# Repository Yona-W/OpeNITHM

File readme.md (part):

# OpeNITHM

This repository contails files related to OpeNITHM.

Firmware, schematics, board layout, and CAD files are included in this repo. Please see the CAD directory for the original 3d printed version, or the v2-cad directory for the laser cut version. 

## List of Hardware

In the `CAD\STL` folder, you will find numerous parts that must be 3D printed.

Please check out [the wiki](https://github.com/veroxzik/OpeNITHM/wiki/File-Explanation) for more information.

| Part | Qty |
| --- |:---:|
| Center Frame | 1 |
| Right Frame | 1 |
| Left Frame | 1 |
| Key Dual 2.5mm **OR** Key Dual 3mm<sup>1</sup> | 16 |
| LED Support Peg | 16 |
| Sensor Rail | 2 |
| Sensor Spacer Left<sup>2</sup> | 1 |
| Sensor Base Left<sup>2</sup> **OR** Integrated Sensor Base Left<sup>2</sup> | 1 |
| Sensor Cover Left<sup>2</sup> | 1 |
| Integrated Frame Mount Left<sup>2,3</sup> | 1 |

**NOTES:** 
1. Use 2.5mm for 3/32" and 3mm for 1/8" acrylic. 
2. Print out mirrored version of these parts as well.
3. Only print the frame mount if you are using the integrated sensor.

The non-printed materials and hardware include:

| Part                                                                       | Qty |
| --- |:---:|
| 4-40 Flat Head Screw, length 3/16" to 5/16" will work **OR** M3 equivalent | 2   |
| Top Acrylic Plate<sup>1</sup> (472mm x 112mm)                              | 1   |
| Key Acrylic<sup>1</sup> (103.5mm x 26mm)                                   | 16  |
| Copper Tape, cut into rectangles 95mm x 26mm                               | 16  |

**NOTES:**
1. Use 2.5mm (3/32") **OR** 3mm (1/8") acrylic. Use the same acrylic for top plate and keys.

## List of Electronics

OpeNITHM is designed for the Teensy LC.

#### Why use Teensy and not Arduino?

The biggest reason is that Teensy has built in capacitive sensing, which is how OpeNITHM fuctions. You have to fake it on Arduino using very controlled analog reads, and it is nowhere near as sensitive. In my (VXZK's) experience, it was simply impossible to use an Arduino to do the capacitive sensing required for this project.

I chose the Teensy LC as it is the lowest cost Teensy model available with capacitive sensing. The firmware and PCB are designed for this board alone; significant modifications may be required for any other version.

There is an alternative build using an Arduino Pro Micro and 2 MPR121s as a branch in this repo, but it is not maintained and not recommended. You're on your own with that one!

### Teensy LC Build

Links are mostly suggestions (except the Teensy, which is only officially available through the PJRC site and authorized resellers).  
(VXZK: I've heard a lot of trouble regarding good quality IR leds and phototransistors, so I've included specific links to the ones I purchased and has worked well for me.)  

The links below also assume you want to socket your Teensy and multiplexers for later use. You can solder them directly, if you'd like.  
If you are going to solder your sensors directly to the PCB, it is not necessary buy the 0.1" Pin Header, Right Angle. Otherwise, include female 0.1" sockets for your sensors (commonly referred to as Dupont connectors).  

| Part | Link | Qty |
| --- | --- |:---:|
| Teensy LC | https://www.pjrc.com/store/teensylc.html | 1 |
| Teensy LC Breakout Board | this Github, Circuit-Teensy32 folder contains gerbers | 1 |
| 74HC4051 Multiplexer Breakout Board | [Aliexpress][1] | 4 |
| 0.1" Pin Header, 1 row, 40 pos | [Aliexpress (qty 10)][2] | 2 |
| 0.1" Pin Header, Right Angle, 2 row, 24 pos | [LCSC][3] | 2 |
| 0.1" Socket, Straight, 1 row, 14 pos | [LCSC][4] | 2 |
| 0.1" Socket, Straight, 1 row, 5 pos | [LCSC][5] | 2 |
| 0.1" Socket, Straight, 1 row, 11 pos | [LCSC][6] | 2 |
| 0.1" Socket, Straight, 1 row, 8 pos | [LCSC][7] | 2 |
| 51k ohm Resistor, 1/6W or 1/8W | LCSC or Aliexpress | 6 |
| 33 ohm Resistor, 1/4W, 1/6W, or 1/8W | LCSC or Aliexpress | 3 |
| 1m WS2812B RGB 5V LED Strip, 30LED Per Meter | [Aliexpress][8] | 1 |
| IR LED and Phototransistor | [Ebay (Qty 20 pairs)][9] | 6 |

[1]: https://www.aliexpress.com/item/32807771098.html
[2]: https://www.aliexpress.com/item/665534073.html
[3]: https://lcsc.com/product-detail/New-Arrivals_XFCN-PZ254R-12-24P_C492440.html
[4]: https://lcsc.com/product-detail/Pin-Header-Female-Header_Boom-Precision-Elec-Female-header-2-54-1-14P_C52711.html
[5]: https://lcsc.com/product-detail/Pin-Header-Female-Header_Boom-Precision-Elec-2-54mm-1-5p-Female-header_C50950.html
[6]: https://lcsc.com/product-detail/Pin-Header-Female-Header_Changjiang-Connectors-A2541HWV-11P_C225508.html
[7]: https://lcsc.com/product-detail/Pin-Header-Female-Header_Boom-Precision-Elec-2-54mm-1-8P-Straight-Female-header_C27438.html
[8]: https://www.aliexpress.com/item/2036819167.html
[9]: https://www.ebay.com/itm/40pcs-5mm-Infrared-LED-940nm-Emitter-Diode-and-IR-Receiver-Set/252235145540

## Board Revision and Sensors

As of 2020-07-17, the recommended board version is v2.1, which features inputs for 32 sensors. This best replicates the feeling of the arcade. Previous versions used 16 sensors. If you still wish to make a 16 key version, you can order the v2.1 but only populate two of the multiplexers. This is not really recommended.

## Installing on Teensy LC

**NOTE:** This firmware is *only* written to work for the Teensy LC. Do *not* use Teensy 2.0 or Teensy 3.x

Skip this section if you are using a Pro Micro.

Locate your `arduino` folder (usually `C:\Program Files (x86)\arduino`).

#### I have a fresh install of Teensyduino, or have never modified my USB profiles

Copy `Firmware/Teensy/boards.txt` to `arduino\hardware\teensy\avr\` and overwrite the existing.

Copy `Firmware/Teensy/teensy3` to `arduino\hardware\teensy\avr\cores\teensy3` and overwrite any conflicts.

Copy `Firmware/FastLED/WS2812Serial.cpp` and `Firmware/FastLED/WS2812Serial.h` to `arduino\hardware\teensy\avr\libraries\WS2812Serial` and overwrite the existing.

Copy `Firmware/FastLED/FastLED.cpp` and `Firmware/FastLED/FastLED.h` to `[My Documents]\Arduino\libraries\FastLED\` and overwrite the existing.

#### I am applying the changes manually

(It is easier to copy and paste from the files in `Firmware/Teensy` instead of through here, the below is just for reference.)

Add `usb_nkro.c` and `usb_nkro.h` to `arduino\hardware\teensy\avr\cores\teensy3`

In `arduino\hardware\teesny\avr\boards.txt` add lines 1175-1179

```c
1175    teensyLC.menu.usb.nkrokeyboard=NKRO Keyboard
1176    teensyLC.menu.usb.nkrokeyboard.build.usbtype=USB_NKRO
1177    teensyLC.menu.usb.nkrokeyboard.fake_serial=teensy_gateway
1178    teensyLC.menu.usb.serialnkrokeyboard=Serial + NKRO Keyboard
1179    teensyLC.menu.usb.serialnkrokeyboard.build.usbtype=USB_SERIAL_NKRO

In `arduino\hardware\teensy\avr\cores\teensy3\WProgram.h` add line 59

```c
58    #include "usb_joystick.h"
59    #include "usb_nkro.h"
60    #include "usb_midi.h"
```

In `arduino\hardware\teensy\avr\cores\teensy3\usb_inst.cpp` add lines 75-77

```c
72    usb_serial_class Serial;
73    #endif
74    
75    #ifdef NKRO_INTERFACE
76    usb_nkro_class Nkro;
77    #endif
78    
79    #else // F_CPU < 20 MHz
```

In `arduino\hardware\teensy\avr\cores\teensy3\usb_dev.h` add lines 93-98

```c
90    extern volatile uint8_t keyboard_leds;
91    #endif
92    
93    #ifdef NKRO_INTERFACE
94    extern uint8_t nkro_report_data[NKRO_SIZE];
95    extern uint8_t nkro_protocol;
96    extern uint8_t nkro_idle_config;
97    extern uint8_t nkro_idle_count;
98    #endif
99    
100   #ifdef MIDI_INTERFACE
```

In `arduino\hardware\teensy\avr\cores\teensy3\usb_desc.h` add lines 868-948

```c
866      #define ENDPOINT15_CONFIG	ENDPOINT_TRANSMIT_ONLY
867    
868    #elif defined(USB_NKRO)
869      #define VENDOR_ID		0x16C0
870      #define PRODUCT_ID		0x04D0
871      #define MANUFACTURER_NAME	{'T','e','e','n','s','y','d','u','i','n','o'}
872      #define MANUFACTURER_NAME_LEN	11
873      #define PRODUCT_NAME		{'N','K','R','O',' ','K','e','y','b','o','a','r','d'}
874     #define PRODUCT_NAME_LEN	13
875      #define EP0_SIZE		64
876      #define NUM_ENDPOINTS         5
877      #define NUM_USB_BUFFERS	14
878      #define NUM_INTERFACE		4
879      #define SEREMU_INTERFACE      1	// Serial emulation
880      #define SEREMU_TX_ENDPOINT    1
881      #define SEREMU_TX_SIZE        64
882      #define SEREMU_TX_INTERVAL    1
883      #define SEREMU_RX_ENDPOINT    2
884      #define SEREMU_RX_SIZE        32
885      #define SEREMU_RX_INTERVAL    2
886      #define KEYBOARD_INTERFACE    0	// Keyboard
887      #define KEYBOARD_ENDPOINT     3
888      #define KEYBOARD_SIZE         8
889      #define KEYBOARD_INTERVAL     1
890      #define KEYMEDIA_INTERFACE    2	// Keyboard Media Keys
891      #define KEYMEDIA_ENDPOINT     4
892      #define KEYMEDIA_SIZE         8
893      #define KEYMEDIA_INTERVAL     4
894      #define NKRO_INTERFACE        3	// NKRO Keyboard
895      #define NKRO_ENDPOINT         5
896      #define NKRO_SIZE             32
897      #define NKRO_REPORT_KEYS		( NKRO_SIZE - 1 )
898      #define NKRO_INTERVAL         1
899      #define ENDPOINT1_CONFIG	ENDPOINT_TRANSMIT_ONLY
900      #define ENDPOINT2_CONFIG	ENDPOINT_RECEIVE_ONLY
901      #define ENDPOINT3_CONFIG	ENDPOINT_TRANSMIT_ONLY
902      #define ENDPOINT4_CONFIG	ENDPOINT_TRANSMIT_ONLY
903      #define ENDPOINT5_CONFIG	ENDPOINT_TRANSMIT_ONLY
904      #define ENDPOINT6_CONFIG	ENDPOINT_TRANSMIT_ONLY
905
906    #elif defined(USB_SERIAL_NKRO)
907      #define VENDOR_ID		0x16C0
908      #define PRODUCT_ID		0x0487
909      #define DEVICE_CLASS		0xEF
910      #define DEVICE_SUBCLASS	0x02
911      #define DEVICE_PROTOCOL	0x01
912      #define MANUFACTURER_NAME	{'T','e','e','n','s','y','d','u','i','n','o'}
913      #define MANUFACTURER_NAME_LEN	11
914      #define PRODUCT_NAME		{'S','e','r','i','a','l','/','N','K','R','O',' ','K','e','y','b','o','a','r','d'}
915      #define PRODUCT_NAME_LEN	20
916      #define EP0_SIZE		64
917      #define NUM_ENDPOINTS         6
918      #define NUM_USB_BUFFERS	14
919      #define NUM_INTERFACE		5
920      #define CDC_IAD_DESCRIPTOR	1
921      #define CDC_STATUS_INTERFACE	0
922      #define CDC_DATA_INTERFACE	1	// Serial
923      #define CDC_ACM_ENDPOINT	2
924      #define CDC_RX_ENDPOINT       3
925      #define CDC_TX_ENDPOINT       4
926      #define CDC_ACM_SIZE          16
927      #define CDC_RX_SIZE           64
928      #define CDC_TX_SIZE           64
929      #define KEYBOARD_INTERFACE    2	// Keyboard
930      #define KEYBOARD_ENDPOINT     1
931      #define KEYBOARD_SIZE         8
932      #define KEYBOARD_INTERVAL     1
933      #define KEYMEDIA_INTERFACE    3	// Keyboard Media Keys
934      #define KEYMEDIA_ENDPOINT     5
935      #define KEYMEDIA_SIZE         8
936      #define KEYMEDIA_INTERVAL     4
937      #define NKRO_INTERFACE        4	// NKRO Keyboard
938      #define NKRO_ENDPOINT         6
939      #define NKRO_SIZE             32
940      #define NKRO_REPORT_KEYS		( NKRO_SIZE - 1 )
941      #define NKRO_INTERVAL         1
942      #define ENDPOINT1_CONFIG	ENDPOINT_TRANSMIT_ONLY
943      #define ENDPOINT2_CONFIG	ENDPOINT_TRANSMIT_ONLY
944      #define ENDPOINT3_CONFIG	ENDPOINT_RECEIVE_ONLY
945      #define ENDPOINT4_CONFIG	ENDPOINT_TRANSMIT_ONLY
946      #define ENDPOINT5_CONFIG	ENDPOINT_TRANSMIT_ONLY
947      #define ENDPOINT6_CONFIG	ENDPOINT_TRANSMIT_ONLY
948    #endif
949    
950    #ifdef USB_DESC_LIST_DEFINE
```

In `arduino\hardware\teensy\avr\cores\teensy3\usb_desc.c` add lines 239-265

```c
236    };
237    #endif
238    
239    #ifdef NKRO_INTERFACE
240    // Via https://dawnmist.dreamwidth.org/1250.html
241    static uint8_t nkro_hid_report_desc[] = {
242            0x05, 0x01, // Usage Page (Generic Desktop),
243            0x09, 0x06, // Usage (Keyboard),
244            0xA1, 0x01, // Collection (Application),
245            // bitmap of modifiers
246            0x75, 0x01, // Report Size (1),
247            0x95, 0x08, // Report Count (8),
248            0x05, 0x07, // Usage Page (Key Codes),
249            0x19, 0xE0, // Usage Minimum (224),
250            0x29, 0xE7, // Usage Maximum (231),
251            0x15, 0x00, // Logical Minimum (0),
252            0x25, 0x01, // Logical Maximum (1),
253            0x81, 0x02, // Input (Data, Variable, Absolute), ;Modifier byte
254            // bitmap of keys
255            0x95, NKRO_REPORT_KEYS*8, // Report Count (),
256            0x75, 0x01, // Report Size (1),
257            0x15, 0x00, // Logical Minimum (0),
258            0x25, 0x01, // Logical Maximum(1),
259            0x05, 0x07, // Usage Page (Key Codes),
260            0x19, 0x00, // Usage Minimum (0),
261            0x29, NKRO_REPORT_KEYS*8-1, // Usage Maximum (),
262            0x81, 0x02, // Input (Data, Variable, Absolute),
263            0xc0 // End Collection
264    };
265    #endif
266    
267    #ifdef JOYSTICK_INTERFACE
268    #if JOYSTICK_SIZE == 12
```

In `arduino\hardware\teensy\avr\cores\teensy3\usb_desc.c` add lines 603-610 and modify line 612

```c
600    #define MULTITOUCH_INTERFACE_DESC_SIZE	0
601    #endif
602    
603    // Via https://dawnmist.dreamwidth.org/1250.html
604    #define NKRO_INTERFACE_DESC_POS	MULTITOUCH_INTERFACE_DESC_POS+MULTITOUCH_INTERFACE_DESC_SIZE
605    #ifdef  NKRO_INTERFACE
606    #define NKRO_INTERFACE_DESC_SIZE	9+9+7
607    #define NKRO_HID_DESC_OFFSET	NKRO_INTERFACE_DESC_POS+9
608    #else
609    #define NKRO_INTERFACE_DESC_SIZE	0
610    #endif
611    
612    #define CONFIG_DESC_SIZE		NKRO_INTERFACE_DESC_POS+NKRO_INTERFACE_DESC_SIZE
613    
614    
615    
616    // **************************************************************
```

In `arduino\hardware\teensy\avr\cores\teensy3\usb_desc.c` add lines 1131-1158

```c
1129   #endif // JOYSTICK_INTERFACE
1130   
1131   #ifdef NKRO_INTERFACE
1132           // interface descriptor, USB spec 9.6.5, page 267-269, Table 9-12
1133           9,                                      // bLength
1134           4,                                      // bDescriptorType
1135           NKRO_INTERFACE,                         // bInterfaceNumber
1136           0,                                      // bAlternateSetting
1137           1,                                      // bNumEndpoints
1138           0x03,                                   // bInterfaceClass (0x03 = HID)
1139           0x00,                                   // bInterfaceSubClass (0x01 = Boot)
1140           0x00,                                   // bInterfaceProtocol (0x01 = Keyboard)
1141           0,                                      // iInterface
1142           // HID interface descriptor, HID 1.11 spec, section 6.2.1
1143           9,                                      // bLength
1144           0x21,                                   // bDescriptorType
1145           0x11, 0x01,                             // bcdHID
1146           0,                                      // bCountryCode
1147           1,                                      // bNumDescriptors
1148           0x22,                                   // bDescriptorType
1149           LSB(sizeof(nkro_hid_report_desc)),      // wDescriptorLength
1150           MSB(sizeof(nkro_hid_report_desc)),
1151           // endpoint descriptor, USB spec 9.6.6, page 269-271, Table 9-13
1152           7,                                      // bLength
1153           5,                                      // bDescriptorType
1154           NKRO_ENDPOINT | 0x80,                   // bEndpointAddress
1155           0x03,                                   // bmAttributes (0x03=intr)
1156           NKRO_SIZE, 0,                           // wMaxPacketSize
1157           NKRO_INTERVAL,                          // bInterval
1158   #endif // NKRO_INTERFACE
1159   
1160   #ifdef MTP_INTERFACE
```

In `arduino\hardware\teensy\avr\cores\teensy3\usb_desc.c` add lines 1602-1605

```c
1600           {0x2100, MULTITOUCH_INTERFACE, config_descriptor+MULTITOUCH_HID_DESC_OFFSET, 9},
1601   #endif
1602   #ifdef NKRO_INTERFACE
1603           {0x2200, NKRO_INTERFACE, nkro_hid_report_desc, sizeof(nkro_hid_report_desc)},
1604           {0x2100, NKRO_INTERFACE, config_descriptor+NKRO_HID_DESC_OFFSET, 9},
1605   #endif
1606   #ifdef MTP_INTERFACE
```

In `arduino\hardware\teensy\avr\boards.txt` add lines 1175-1177
```
1174    teensyLC.menu.usb.flightsim.fake_serial=teensy_gateway
1175    teensyLC.menu.usb.nkrokeyboard=NKRO Keyboard
1176    teensyLC.menu.usb.nkrokeyboard.build.usbtype=USB_NKRO
1177    teensyLC.menu.usb.nkrokeyboard.fake_serial=teensy_gateway
1178    teensyLC.menu.usb.disable=No USB
```

## Configuring the Firmware and IDE

There are a number of options built into the firmware to give you flexibility in your implementation. These are presented as preprocessor defines that can be commented and uncommented to fit.

All user-editable defines are in `Config.h`, see the comments for additional information.

If you are not using either the Pro Micro or Teensy LC boards provided in this repo, it may be necessary to change the definitions of the pins, located in `PinConfig.h`.

If you do not have the FastLED and HID-Project libraries installed, do so though the `Tools->Manage Libraries` menu.

#### Compiling

When using a Pro Micro, select `Arduino/Genuino Micro` from `Tools->Board`.

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
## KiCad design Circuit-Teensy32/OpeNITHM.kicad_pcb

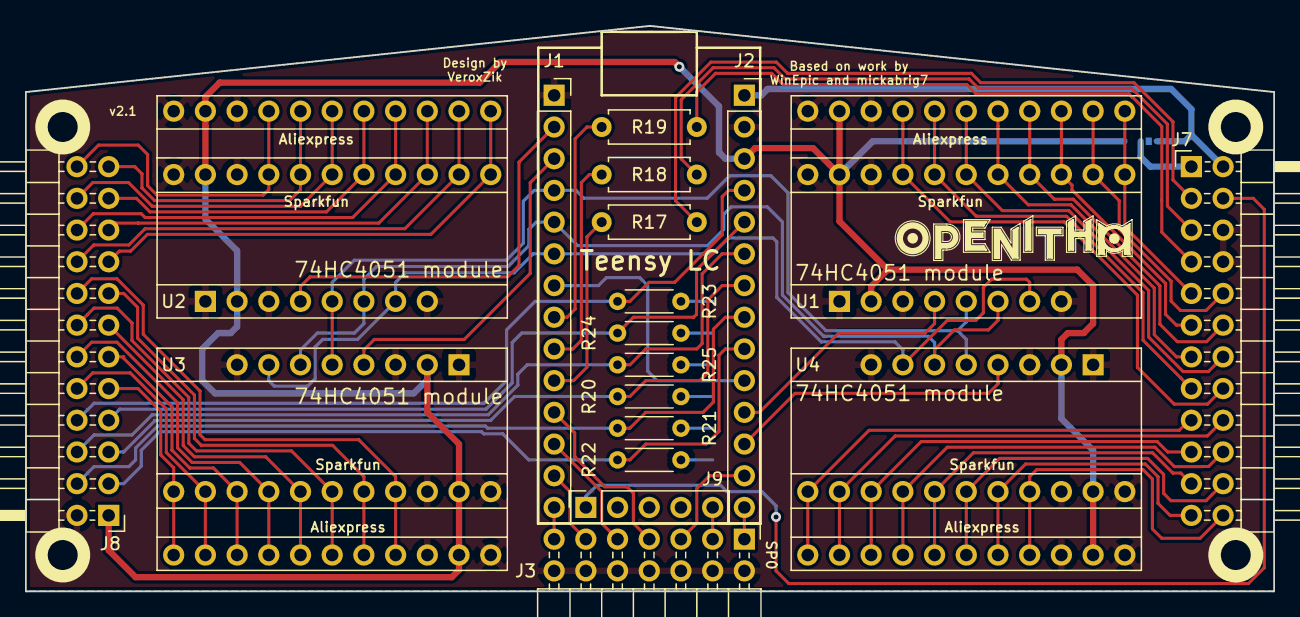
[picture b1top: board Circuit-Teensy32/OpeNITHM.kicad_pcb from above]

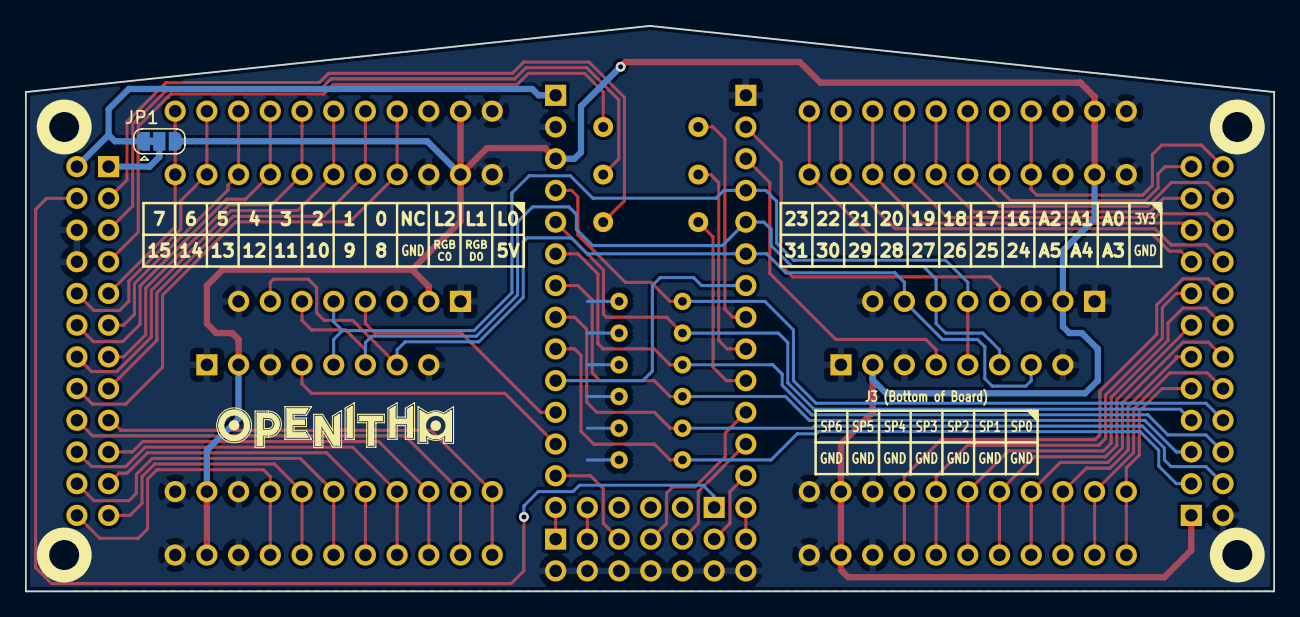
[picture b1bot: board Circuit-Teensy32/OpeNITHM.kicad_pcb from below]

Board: 2 copper layers, 100.0 x 45.3 mm, 26 parts (2 on the bottom side), 64 nets.

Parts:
H1, H2, H3, H4: MountingHole; MountingHole_3.2mm_M3_ISO14580
J1, J2: Conn_01x14; PinSocket_1x14_P2.54mm_Vertical
J3: Conn_02x07_Odd_Even; PinHeader_2x07_P2.54mm_Horizontal
J7, J8: Conn_02x12_Odd_Even; PinHeader_2x12_P2.54mm_Horizontal
J9: Conn_01x05; PinSocket_1x05_P2.54mm_Vertical
JP1: SolderJumper_3_Bridged12; SolderJumper-3_P1.3mm_Bridged12_RoundedPad1.0x1.5mm
LOGO1, LOGO2: Logo; openithm-logo
R17, R18, R19: 33; R_Axial_DIN0207_L6.3mm_D2.5mm_P7.62mm_Horizontal
R20, R21, R22, R23, R24, R25: R_AIR; R_Axial_DIN0204_L3.6mm_D1.6mm_P5.08mm_Horizontal
U1, U2, U3, U4: 74HC4051; 74HC4051_Sparkfun_Aliexpress

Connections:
+3V3: J2.3, J8.1, JP1.3, U1.2, U1.18, U2.2, U2.18, U3.2, U3.18, U4.2, U4.18
+5V: J2.1, J7.2, JP1.1
/AIR_0: J2.9, J8.3, R22.1
/AIR_1: J2.7, J8.5, R20.1
/AIR_2: J2.5, J8.7, R24.1
/AIR_3: J2.8, J8.4, R21.1
/AIR_4: J2.6, J8.6, R25.1
/AIR_5: J2.4, J8.8, R23.1
/KEY_0: J7.10, U1.10
/KEY_1: J7.12, U1.12
/KEY_2: J7.14, U1.14
/KEY_3: J7.16, U1.16
/KEY_4: J7.18, U4.10
/KEY_5: J7.20, U4.12
/KEY_6: J7.22, U4.14
/KEY_7: J7.24, U4.16
/KEY_8: J7.9, U1.9
/KEY_9: J7.11, U1.11
/KEY_10: J7.13, U1.13
/KEY_11: J7.15, U1.15
/KEY_12: J7.17, U4.9
/KEY_13: J7.19, U4.11
/KEY_14: J7.21, U4.13
/KEY_15: J7.23, U4.15
/KEY_16: J8.9, U3.9
/KEY_17: J8.11, U3.11
/KEY_18: J8.13, U3.13
/KEY_19: J8.15, U3.15
/KEY_20: J8.17, U2.9
/KEY_21: J8.19, U2.11
/KEY_22: J8.21, U2.13
/KEY_23: J8.23, U2.15
/KEY_24: J8.10, U3.10
/KEY_25: J8.12, U3.12
/KEY_26: J8.14, U3.14
/KEY_27: J8.16, U3.16
/KEY_28: J8.18, U2.10
/KEY_29: J8.20, U2.12
/KEY_30: J8.22, U2.14
/KEY_31: J8.24, U2.16
/LED_0: J1.10, R17.2
/LED_0_OUT: J7.3, R17.1
/LED_1: J1.9, R18.2
/LED_1_OUT: J7.5, R18.1
/LED_2: J1.8, R19.2
/LED_2_OUT: J7.7, R19.1
/MUX_0: J1.4, U1.5, U2.5, U3.5, U4.5
/MUX_1: J1.5, U1.6, U2.6, U3.6, U4.6
/MUX_2: J1.6, U1.7, U2.7, U3.7, U4.7
/RGB_DO: J1.7, J2.10
/RGB_DO_BUF: J7.4, J9.1
/SPARE_0: J2.14, J3.1
/SPARE_1: J3.3, J9.5
/SPARE_2: J2.13, J3.5
/SPARE_3: J1.11, J3.7
/SPARE_4: J1.12, J3.9
/SPARE_5: J1.13, J3.11
/SPARE_6: J1.14, J3.13
/TOUCH_0: J2.11, U1.4
/TOUCH_1: J1.2, U2.4
/TOUCH_2: J1.3, U3.4
/TOUCH_3: J2.12, U4.4
GND: J1.1, J2.2, J3.2, J3.4, J3.6, J3.8, J3.10, J3.12, J3.14, J7.6, J7.8, J8.2, R20.2, R21.2, R22.2, R23.2, R24.2, R25.2, U1.1, U1.3, U1.8, U1.17, U1.19, U2.1, U2.3, U2.8, U2.17, U2.19, U3.1, U3.3, U3.8, U3.17, U3.19, U4.1, U4.3, U4.8, U4.17, U4.19
VCC: J7.1, JP1.2

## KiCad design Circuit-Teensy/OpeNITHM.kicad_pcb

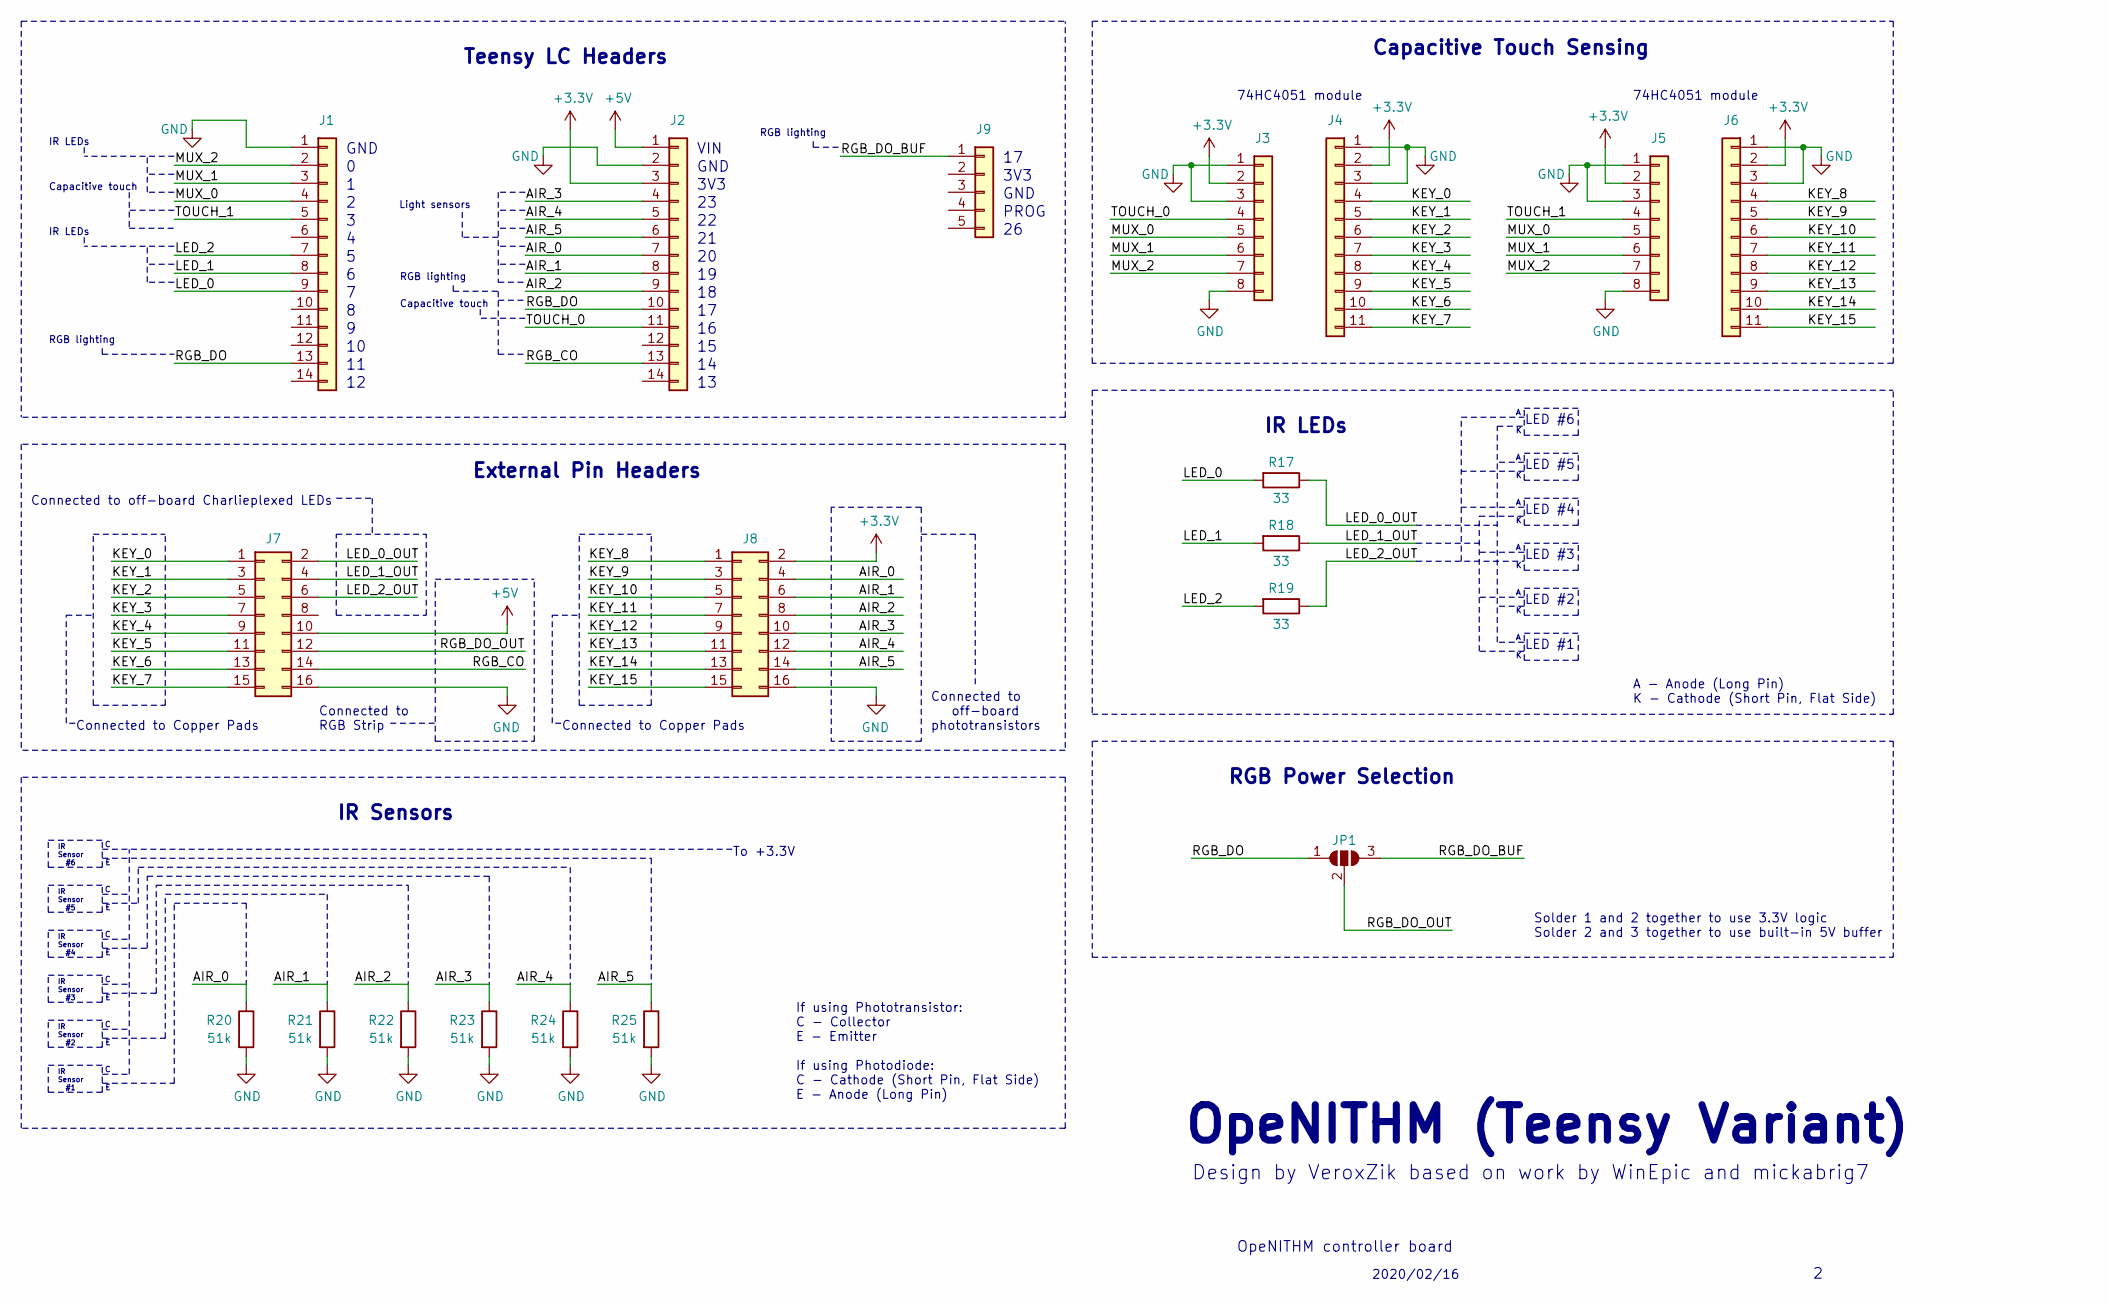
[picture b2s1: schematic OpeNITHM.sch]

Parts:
J1, J2: Conn_01x14; PinSocket_1x14_P2.54mm_Vertical
J3, J5: Conn_01x08; PinSocket_1x08_P2.54mm_Vertical
J4, J6: Conn_01x11; PinSocket_1x11_P2.54mm_Vertical
J7, J8: Conn_02x08_Odd_Even; PinHeader_2x08_P2.54mm_Horizontal
J9: Conn_01x05; PinSocket_1x05_P2.54mm_Vertical
JP1: SolderJumper_3_Open; SolderJumper-3_P1.3mm_Open_RoundedPad1.0x1.5mm
R17, R18, R19: 33; R_Axial_DIN0207_L6.3mm_D2.5mm_P7.62mm_Horizontal
R20, R21, R22, R23, R24, R25: 51k; R_Axial_DIN0204_L3.6mm_D1.6mm_P5.08mm_Horizontal

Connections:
+3V3: J2.3, J3.2, J4.2, J5.2, J6.2, J8.2; also elsewhere on the board
+5V: J2.1, J7.10
/AIR_0: J2.7, J8.4, R20.1
/AIR_1: J2.8, J8.6, R21.1
/AIR_2: J2.9, J8.8, R22.1
/AIR_3: J2.4, J8.10, R23.1
/AIR_4: J2.5, J8.12, R24.1
/AIR_5: J2.6, J8.14, R25.1
/KEY_0: J4.4, J7.1; also elsewhere on the board
/KEY_1: J4.5, J7.3; also elsewhere on the board
/KEY_2: J4.6, J7.5; also elsewhere on the board
/KEY_3: J4.7, J7.7; also elsewhere on the board
/KEY_4: J4.8, J7.9; also elsewhere on the board
/KEY_5: J4.9, J7.11; also elsewhere on the board
/KEY_6: J4.10, J7.13; also elsewhere on the board
/KEY_7: J4.11, J7.15; also elsewhere on the board
/KEY_8: J6.4, J8.1; also elsewhere on the board
/KEY_9: J6.5, J8.3; also elsewhere on the board
/KEY_10: J6.6, J8.5; also elsewhere on the board
/KEY_11: J6.7, J8.7; also elsewhere on the board
/KEY_12: J6.8, J8.9; also elsewhere on the board
/KEY_13: J6.9, J8.11; also elsewhere on the board
/KEY_14: J6.10, J8.13; also elsewhere on the board
/KEY_15: J6.11, J8.15; also elsewhere on the board
/LED_0: J1.9, R17.2
/LED_0_OUT: J7.2, R17.1
/LED_1: J1.8, R18.2
/LED_1_OUT: J7.4, R18.1
/LED_2: J1.7, R19.2
/LED_2_OUT: J7.6, R19.1
/MUX_0: J1.4, J3.5, J5.5
/MUX_1: J1.3, J3.6, J5.6
/MUX_2: J1.2, J3.7, J5.7
/RGB_CO: J2.13, J7.14
/RGB_DO: J1.13, J2.10, JP1.1 (A)
/RGB_DO_BUF: J9.1, JP1.3 (B)
/RGB_DO_OUT: J7.12, JP1.2 (C)
/TOUCH_0: J2.11, J3.4
/TOUCH_1: J1.5, J5.4
GND: J1.1, J2.2, J3.1, J3.3, J3.8, J4.1, J4.3, J5.1, J5.3, J5.8, J6.1, J6.3, J7.16, J8.16, R20.2, R21.2, R22.2, R23.2, R24.2, R25.2; also elsewhere on the board

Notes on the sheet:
Capacitive Touch Sensing
Teensy LC Headers
RGB lighting
2020/02/16
OpeNITHM controller board
OpeNITHM (Teensy Variant)
Design by VeroxZik based on work by WinEpic and mickabrig7
Connected to off-board phototransistors
IR Sensors
IR LEDs
LED #1
74HC4051 module
LED #2
LED #3
LED #4
LED #5
LED #6
IR Sensor #6
GND
VIN
3V3
Capacitive touch
PROG
External Pin Headers
Connected to off-board Charlieplexed LEDs
RGB Power Selection
Connected to Copper Pads
Connected to RGB Strip
A - Anode (Long Pin) K - Cathode (Short Pin, Flat Side)
Solder 1 and 2 together to use 3.3V logic Solder 2 and 3 together to use built-in 5V buffer
To +3.3V
If using Phototransistor: C - Collector E - Emitter If using Photodiode: C - Cathode (Short Pin, Flat Side) E - Anode (Long Pin)
IR Sensor #5
IR Sensor #4
IR Sensor #3
IR Sensor #2
IR Sensor #1
Light sensors

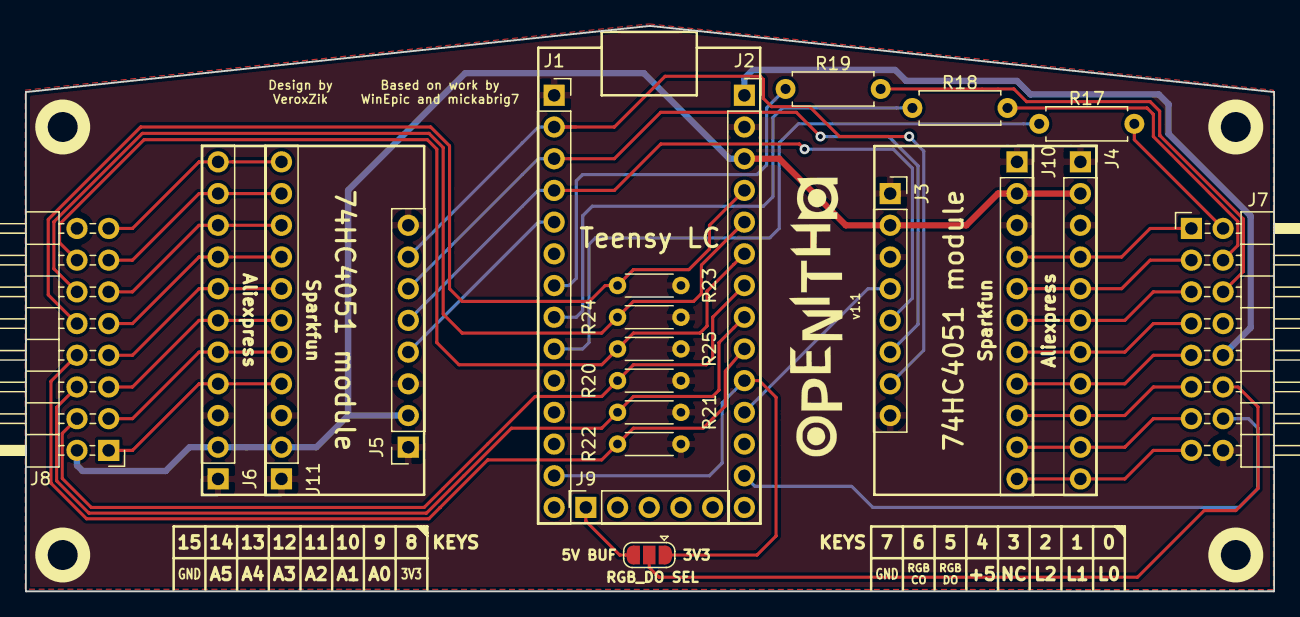
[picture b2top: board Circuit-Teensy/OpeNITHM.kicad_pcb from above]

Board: 2 copper layers, 100.0 x 45.3 mm, 25 parts (0 on the bottom side), 40 nets.

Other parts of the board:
J10, J11: Conn_01x11; PinSocket_1x11_P2.54mm_Vertical
MH1, MH2, MH3, MH4: MountingHole; MountingHole_3.2mm_M3

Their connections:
+3V3: J10.2, J11.2; also elsewhere on the board
/KEY_0: J10.4; also elsewhere on the board
/KEY_1: J10.5; also elsewhere on the board
/KEY_2: J10.6; also elsewhere on the board
/KEY_3: J10.7; also elsewhere on the board
/KEY_4: J10.8; also elsewhere on the board
/KEY_5: J10.9; also elsewhere on the board
/KEY_6: J10.10; also elsewhere on the board
/KEY_7: J10.11; also elsewhere on the board
/KEY_8: J11.4; also elsewhere on the board
/KEY_9: J11.5; also elsewhere on the board
/KEY_10: J11.6; also elsewhere on the board
/KEY_11: J11.7; also elsewhere on the board
/KEY_12: J11.8; also elsewhere on the board
/KEY_13: J11.9; also elsewhere on the board
/KEY_14: J11.10; also elsewhere on the board
/KEY_15: J11.11; also elsewhere on the board
GND: J10.1, J10.3, J11.1, J11.3; also elsewhere on the board

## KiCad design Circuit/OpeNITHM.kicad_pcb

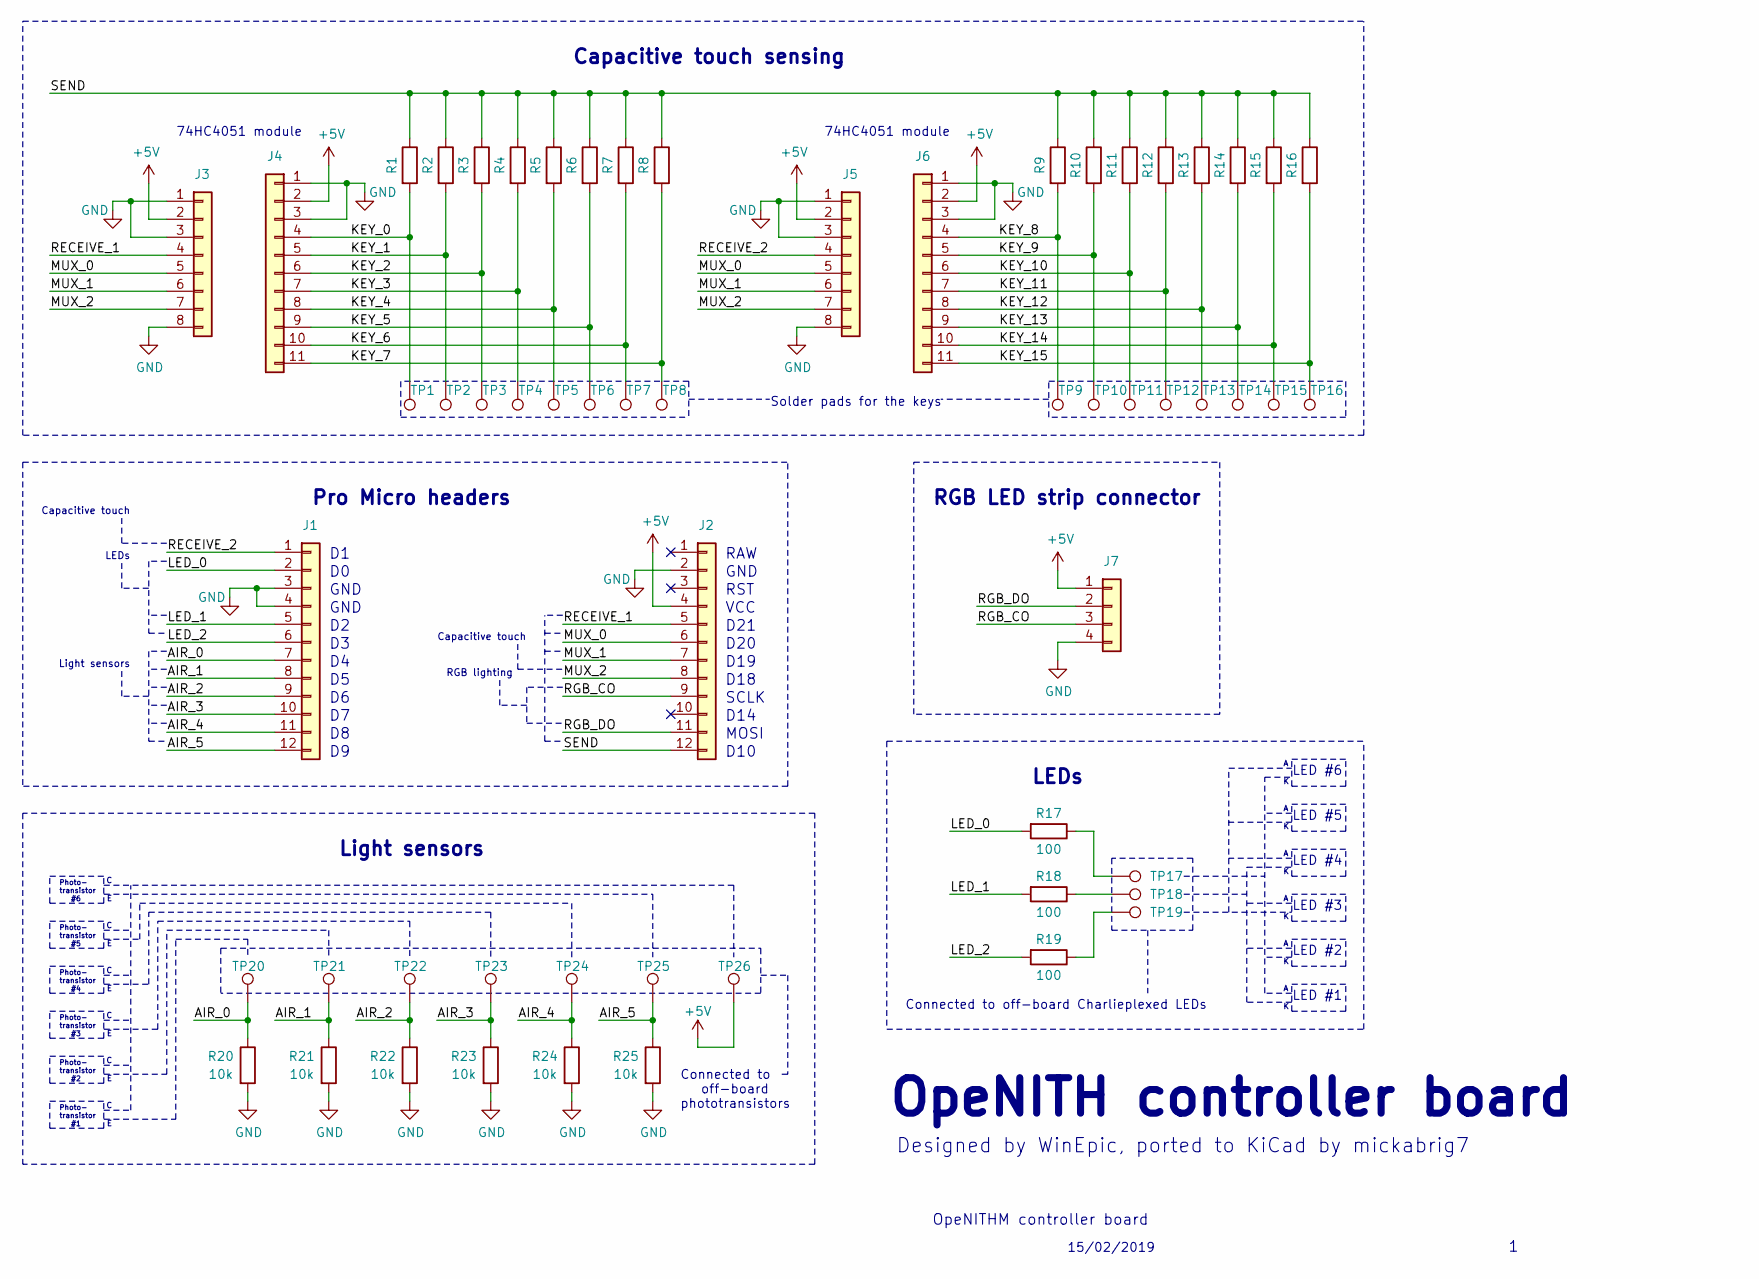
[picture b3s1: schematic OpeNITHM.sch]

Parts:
J1, J2: Conn_01x12; PinSocket_1x12_P2.54mm_Vertical
J3, J5: Conn_01x08; PinSocket_1x08_P2.54mm_Vertical
J4, J6: Conn_01x11; PinSocket_1x11_P2.54mm_Vertical
J7: Conn_01x04; PinSocket_1x04_P2.54mm_Vertical
R1, R2, R3, R4, R5, R6, R7, R8, R9, R10, R11, R12, R13, R14, R15, R16: 6.8M; R_Axial_DIN0204_L3.6mm_D1.6mm_P5.08mm_Horizontal
R17, R18, R19: 100; R_Axial_DIN0204_L3.6mm_D1.6mm_P5.08mm_Horizontal
R20, R21, R22, R23, R24, R25: 10k; R_Axial_DIN0204_L3.6mm_D1.6mm_P5.08mm_Horizontal
TP1, TP2, TP3, TP4, TP5, TP6, TP7, TP8, TP9, TP10, TP11, TP12, TP13, TP14, TP15, TP16, TP17, TP18, TP19, TP20, TP21, TP22, TP23, TP24, TP25, TP26: TestPoint; SolderWirePad_1x01_Drill1mm_Diameter2mm

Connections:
+5V: J2.4, J3.2, J4.2, J5.2, J6.2, J7.1, TP26.1
/AIR_0: J1.7, R20.1, TP20.1
/AIR_1: J1.8, R21.1, TP21.1
/AIR_2: J1.9, R22.1, TP22.1
/AIR_3: J1.10, R23.1, TP23.1
/AIR_4: J1.11, R24.1, TP24.1
/AIR_5: J1.12, R25.1, TP25.1
/KEY_0: J4.4, R1.2, TP1.1
/KEY_1: J4.5, R2.2, TP2.1
/KEY_2: J4.6, R3.2, TP3.1
/KEY_3: J4.7, R4.2, TP4.1
/KEY_4: J4.8, R5.2, TP5.1
/KEY_5: J4.9, R6.2, TP6.1
/KEY_6: J4.10, R7.2, TP7.1
/KEY_7: J4.11, R8.2, TP8.1
/KEY_9: J6.5, R10.2, TP10.1
/KEY_10: J6.6, R11.2, TP11.1
/KEY_11: J6.7, R12.2, TP12.1
/KEY_12: J6.8, R13.2, TP13.1
/KEY_13: J6.9, R14.2, TP14.1
/KEY_14: J6.10, R15.2, TP15.1
/KEY_15: J6.11, R16.2, TP16.1
/LED_0: J1.2, R17.2
/LED_1: J1.5, R18.2
/LED_2: J1.6, R19.2
/MUX_0: J2.6, J3.5, J5.5
/MUX_1: J2.7, J3.6, J5.6
/MUX_2: J2.8, J3.7, J5.7
/RECEIVE_1: J2.5, J3.4
/RECEIVE_2: J1.1, J5.4
/RGB_CO: J2.9, J7.3
/RGB_DO: J2.11, J7.2
GND: J1.3, J1.4, J2.2, J3.1, J3.3, J3.8, J4.1, J4.3, J5.1, J5.3, J5.8, J6.1, J6.3, J7.4, R20.2, R21.2, R22.2, R23.2, R24.2, R25.2
unnamed: R17.1, TP17.1
unnamed: R18.1, TP18.1
unnamed: R19.1, TP19.1

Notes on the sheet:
Capacitive touch sensing
Pro Micro headers
RGB LED strip connector
Capacitive touch
RGB lighting
Light sensors
GND
RAW
RST
VCC
D21
D20
D19
D18
SCLK
D14
MOSI
D10
15/02/2019
OpeNITHM controller board
OpeNITH controller board
Designed by WinEpic, ported to KiCad by mickabrig7
Connected to off-board phototransistors
LEDs
Connected to off-board Charlieplexed LEDs
LED #1
74HC4051 module
LED #2
LED #3
LED #4
LED #5
LED #6
Solder pads for the keys
Photo- transistor #1
Photo- transistor #2
Photo- transistor #3
Photo- transistor #4
Photo- transistor #5
Photo- transistor #6

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
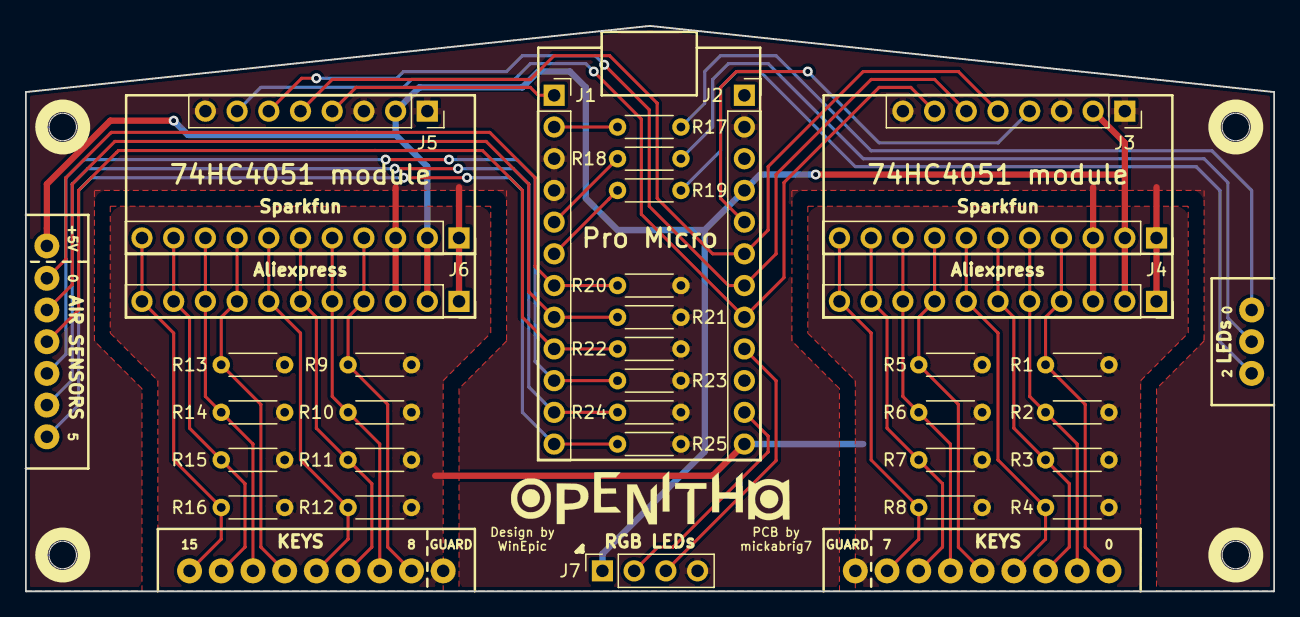
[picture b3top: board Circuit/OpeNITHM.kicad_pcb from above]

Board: 2 copper layers, 100.0 x 45.3 mm, 60 parts (0 on the bottom side), 38 nets.

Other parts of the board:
TP9#2, TP9#3: TestPoint; SolderWirePad_1x01_Drill1mm_Diameter2mm

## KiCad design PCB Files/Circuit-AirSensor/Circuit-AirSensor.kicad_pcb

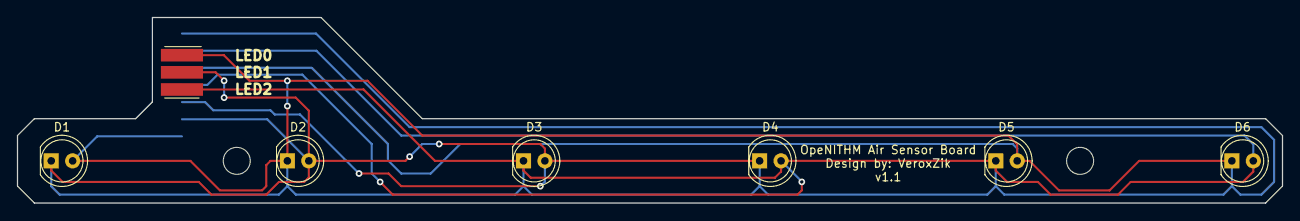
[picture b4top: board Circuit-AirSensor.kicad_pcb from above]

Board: 2 copper layers, 150.0 x 22.0 mm, 10 parts (1 on the bottom side), 7 nets.

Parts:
D1, D2, D3, D4, D5, D6: IR LED; LED_D5.0mm_FlatTop
J1: Conn_01x03; SMD_3Pin
J2: Conn_01x07; SMD_7Pin
MH1, MH2: MountingHole; MountingHole_3.2mm_M3_ISO14580

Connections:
/D1+: D1.2, J2.7
/D1-: D1.1, D2.1, D3.1, D4.1, D5.1, D6.1, J2.1
/D2+: D2.2, J2.6
/D3+: D3.2, J2.5
/D4+: D4.2, J2.4
/D5+: D5.2, J2.3
/D6+: D6.2, J2.2

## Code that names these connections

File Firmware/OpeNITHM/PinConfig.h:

#include "Config.h"

#ifndef _PINCONFIG_h
#define _PINCONFIG_h

// Multiplexer pin settings
#if defined(OPENITHM_V2_0)
#define MUX_0 0
#define MUX_1 1
#define MUX_2 2
#elif defined(OPENITHM_V2_1)
#define MUX_0 2
#define MUX_1 3
#define MUX_2 4
#endif

// Sensor pin settings
#if defined(OPENITHM_V2_0)
#define LED_0 7
#define LED_1 6
#define LED_2 5
#elif defined(OPENITHM_V2_1)
#define LED_0 8
#define LED_1 7
#define LED_2 6
#endif

#define AIR_SENSOR_0_PIN 18
#define AIR_SENSOR_1_PIN 20
#define AIR_SENSOR_2_PIN 22
#define AIR_SENSOR_3_PIN 19
#define AIR_SENSOR_4_PIN 21
#define AIR_SENSOR_5_PIN 23

// Capsense pin settings
#if defined(OPENITHM_V2_0)
#define TOUCH_0 16
#define TOUCH_1 3
#define TOUCH_2 4
#define TOUCH_3 15
#elif defined(OPENITHM_V2_1)
#define TOUCH_0 16
#define TOUCH_1 0
#define TOUCH_2 1
#define TOUCH_3 15
#endif

// Lighting pin settings
#define LED_TYPE    WS2812SERIAL
#define LED_ORDER   BRG

#if defined(OPENITHM_V2_0)
  #define RGBPIN 24
#elif defined(OPENITHM_V2_1)
  #define RGBPIN 5
#endif

#endif  // _PINCONFIG_h

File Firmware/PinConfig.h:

#ifndef _PINCONFIG_h
#define _PINCONFIG_h

#if defined(__AVR_ATmega32U4__) || defined(__AVR_ATmega32u4__)
#define USB
#endif

//#define IR_SENSOR_MULTIPLEXED
//#define IR_SENSOR_ANALOG        // Uncomment if IR sensors are hooked up to analog pins
#define CALIBRATION_SAMPLES 500

// Multiplexer pin settings
#define MUX_0 20
#define MUX_1 19
#define MUX_2 18

// Sensor pin settings
#define LED_0 0
#define LED_1 2
#define LED_2 3

#ifdef IR_SENSOR_MULTIPLEXED
#define SENSOR_IN A0
#else
#define AIR_SENSOR_0_PIN 4
#define AIR_SENSOR_1_PIN 5
#define AIR_SENSOR_2_PIN 6
#define AIR_SENSOR_3_PIN 7
#define AIR_SENSOR_4_PIN 8
#define AIR_SENSOR_5_PIN 9
#endif

// Capsense pin settings
#define RECEIVE_1 21
#define RECEIVE_2 1
#define SEND 10

// Lighting pin settings
#define LED_TYPE    WS2812B
#define LED_ORDER   GRB
#define RGBPIN 16

#endif

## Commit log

2019-01-22 Initial commit to public repo
2019-01-22 Added readme
2019-01-25 Implemented USB Keyboard output (untested)
2019-02-14 Added comments. Updated air sensor code to work with mickabrig7's design.
2019-02-15 Reorganized repository, added circuit schematics
2019-02-18 Fix baud rate and update parseCommand
2019-02-19 CAD v0.1
    Untested
2019-02-19 Fix schematic files
2019-02-19 Add GUARD pads and silk for RGB LED strip connector
2019-02-20 Add basic custom light support
2019-02-20 Fix unnecessary character requirement in serial commands
2019-02-20 Fixed problem compiling for platforms with no USB support
2019-02-21 Updated Logo, Modified frame and keys heavily to reduce size, Reset versions on sensor stands
2019-02-21 Updated frame with tabs, recentered logo
2019-03-06 Added Key model for US Customary
    Should fit 1/8" plexi (untested)
2019-03-08 Updated sensor models
    Now cooler to look at, and able to be clamped to the edge of a desk.
2019-03-10 Updated files
2019-04-19 Updates to match PCB
    Changed pin names to match schematic and PCB per mickabrig7
    Changed default pins numbers to match PCB
    Added ability to use digitalRead for IR sensors
    Changes tabs to 2 spaces (consistent with Arduino standard)
    Fixes build for 32U4 based processors
    (SerialOutput.h/.cpp is untested)
2019-04-19 Fixes (again)
    It didn't build but now it does
    Fixed the USB def for switching between 32U4/328P
    Fixes indents on all files
2019-06-29 Create Firmware Folder
    Arduino IDE will not load OpeNITHM.ino unless it's in a folder named OpeNITHM
2019-06-29 Update Firmware
    Updates README
    Updates firmware to support Teensy LC
    (Selecting the Board in the IDE will switch the code between Pro Micro and Teensy LC)
    Includes the necessary files for the NKRO profile for Teensy.
2019-06-29 Typo in readme
2019-06-30 Typo in usb_desc.c
2019-06-30 Correction to USBOutput.h/.cpp
2019-06-30 Updates to CAD, Upload Teensy Board, Update Readme
2019-07-20 CAD Updates
    Changes tabs to rectangular
2019-07-20 Update CAD
2019-11-09 Added the ability to report back individual IR sensors as keyboard keys
    Uncomment IR_SENSOR_KEY in Config.h to use
2019-11-10 Addition of Serial-controlled RGB lights
    Serial-controlled lights expects the following format:
    Two header bytes, both 0xAA.
    96 LED bytes, in BRG format, starting from the left of the slider and alternating between key and separator.
    Two footer bytes, both 0xDD.
2019-11-22 Adds short calibration warning at startup, updated readme
2019-11-24 Updated resistor recommendation
2019-11-25 Serial Plot is now normalized, updated schematic for 51k recommendation
2019-12-12 Reduced IR sensor delay, Minimized NKRO calls, Rewrote NKRO key commands
2019-12-12 Updated CAD
2019-12-18 Added Air Sensor status indicator on startup
2019-12-18 Remove Pro Micro board files
2020-01-14 Updated IR Led / Phototransistor suggestion
2020-02-16 Added Air Sensor PCB
2020-02-17 Updated main OpeNITHM board to v1.1
    Code has not been updated yet, do not use
2020-02-18 Updated firmware for v1.1 board
2020-03-08 Fairly significant refactor. * Add a new class, AutoTouchboard, which is responsible for calibrating itself on a per-key basis using a user single-touch as the basis for calibration * Overhaul the ma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
2020-03-09 Fix a pin assignment in the v1.1 PinConfig.h. Remove the Touchboard class and make AutoTouchboard the canonical input method for the slider
2020-03-12 Add a single, unified serial processor that can handle both LED updates and config commands. Make lighting mode toggleable during runtime without needing a reflash. Overhaul the analog air sensor thr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
2020-03-12 Fix a silly issue with the sensitivities in AirSensor and AutoTouchboard (integer vs floating point division messing things up)
2020-03-12 Initial commit of the configuration GUI, it still needs a few options added and some slight firmware changes are needed for persisting values to EEPROM and providing the config tool its initial value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
2020-03-12 Make the controller firmware switch between serial and reactive lighting automatically. Start out reactive, switch to serial if a signal comes in, switch back to reactive after 5 seconds of no serial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
2020-03-12 Remove the lighting mode switcher control from the config UI
2020-03-15 Switch to a simple counter for the lights mode timeout instead of using millis() for better performance
2020-03-16 Go back to 150 microsecond delays for the air sensors
2020-03-21 Make the controller save all the configurable values to EEPROM and make the OpeNITHMConfig tool load the values from EEPROM and initialize the UI with the current controller values
2020-03-21 Make the factory reset button actually clear the EEPROM and reset the config values
2020-03-25 Go back to only processing every other light update to better processing
2020-03-29 Make the analog air sensors also calibrate within the constructor, and change up some of the analog air code now that I have a v1.1 to test with
2020-03-29 Fix some analog air calibration logic
2020-07-07 Get my repo up to speed with Nicole's repo (acrylic CAD, lighted key dividers)
2020-07-07 Bring in fuee's changes for DMA LED updates and improved touch input response time. Overhaul the slider and air sensor calibration methods to be better, more consistent, and no longer have 'sensitivi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
2020-07-08 Fixes to the calibration procedure for the air towers
2020-07-08 Made some fixes to air calibration so it saves correctly, and add a config for DMA LEDs so people without still have the right RGB pin and type
2020-07-08 Don't run benchmarking by default
2020-08-01 UNTESTED: Initial support for 32-key builds, along with some general cleanup.
2020-08-02 Fix some issues that were preventing 32-key mode from working correctly
2020-08-02 Fix a bug in 32-key mode that made it possible to read DOUBLE_PRESS on a sensor
2020-08-06 Fix a dumb bug in the AirSensor calibration code for determining if the first 4 keys are held
2020-09-08 Update the CAD for 32k acrylic cons, and account for the AliExpress IR hardware
2020-09-10 Bringing in the PCB revisions for v2.1
2020-09-10 Readme update
2020-10-08 Doing some repo re-organization to make directories clearer
2020-10-08 Remove a *ton* of legacy code. * No more support for boards < v2.0. * No more digital IR inputs * No more 16-key support * Probably other stuff I'm missing
2020-10-08 The slider *finally* calibrates itself, probably needs a bit of tweaking to figure out the proper values for tuning sensitivity
2020-10-08 Slightly better thresholds for slider calibration
2020-10-08 Bring legacy support back. Add slider auto calibration for 16k
2020-10-10 Experimenting with different autocalibration. WIP
2020-10-20 Improving auto calibration for the slider (only tested 32k):
2020-10-21 (*) Make the air towers auto calibrate themselves instead of needing manual calibration (*) Improve the auto calibration for the slider (32k has been tested, 16k has not) (*) Move the calibration rou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
2020-10-21 Forgot to comment some debug statements
2020-10-21 Forgot to initialize the calibration counter for AutoTouchboard
2020-10-21 Making some adjustments to IR auto calibration
2020-10-21 Checkpoint commit
2020-10-30 Fix a couple of very subtle bugs, it seems like air delay < ~125 causes sensor 11 only (?) to read lower during slider calibration than during the main gameplay loop. Also forgot to remove the call t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
2020-11-10 Fixed IR LED labeling on back silkscreen
